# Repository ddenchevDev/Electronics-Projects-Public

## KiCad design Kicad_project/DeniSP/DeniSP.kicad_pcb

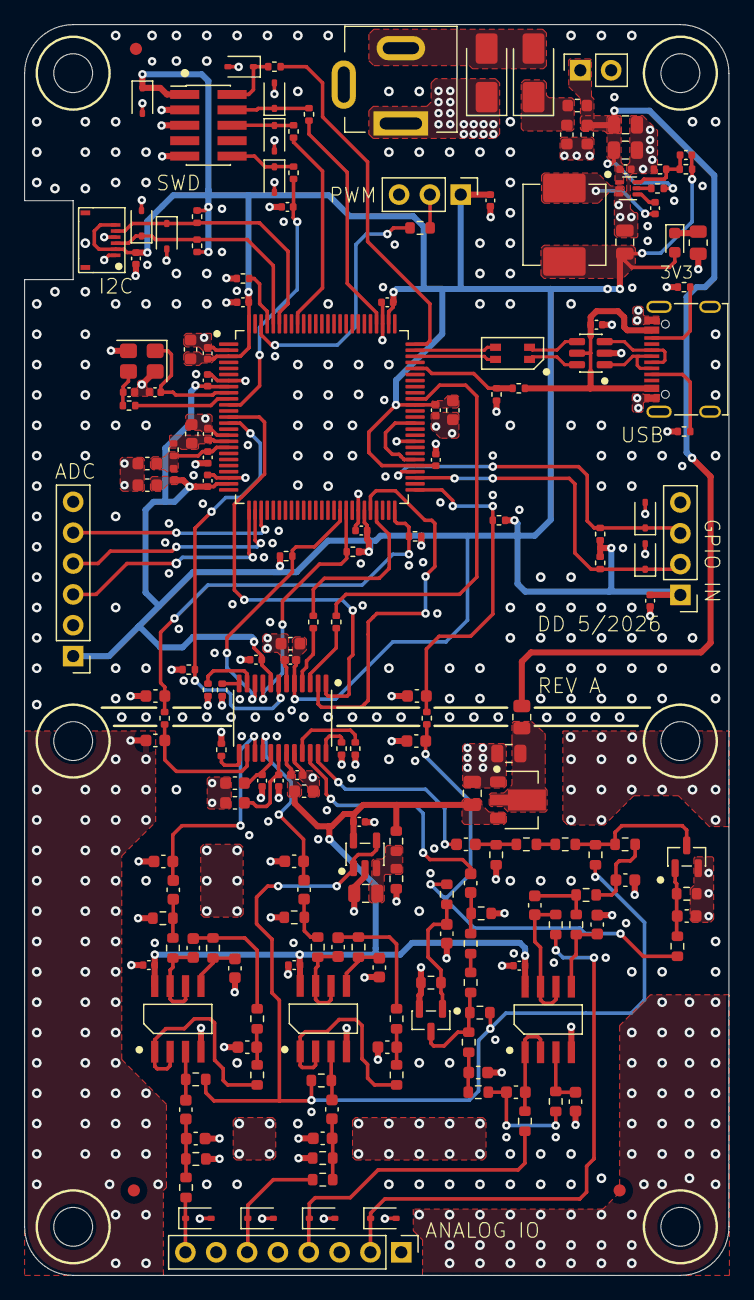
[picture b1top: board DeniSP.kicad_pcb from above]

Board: 4 copper layers, 58.0 x 103.0 mm, 194 parts (0 on the bottom side), 108 nets.

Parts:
C100, C101, C209, C212, C213, C221, C301, C305: 1u; C_0603_1608Metric
C102, C103, C104, C106, C107, C110: 22u; C_0805_2012Metric
C105, C108, C109, C202, C203, C204, C205, C206, C207, C208, C210, C211, C214, C215, C218, C219, C220, C222, C302, C303, C304, C312, C314, C320, C326, C336: 100n; C_0402_1005Metric
C111: 47pf; C_0402_1005Metric
C201, C313, C327, C328, C337, C338: 10u; C_0603_1608Metric
C216, C217: 14p; C_0402_1005Metric
C306, C316: 3.3u; C_0603_1608Metric
C307, C308, C317, C318: 2.2n; C_0603_1608Metric
C309, C319: 330p; C_0603_1608Metric
C310, C311, C341, C342: 2u2; C_0603_1608Metric
C315: 47u; C_0603_1608Metric
C321, C325, C331, C335: 150p; C_0603_1608Metric
C322, C332: 100n; C_0603_1608Metric
C323, C324, C333, C334: 1n; C_0603_1608Metric
C330, C340: DNP; C_0603_1608Metric
D100: SMAJ7.0CA; D_SMA
D101: SS14; D_SMA
D102: GREEN; LED_0603_1608Metric
D202, D203, D204, D205, D206, D207, D208, D209, D210, D300, D301, D302, D303: PESD3V3L1BA,115; D_SOD-323
FL201: WCM3216F2SF-900T04; CMC_3216-4P
H1, H2, H3, H4, H5, H6: MountingHole; MountingHole_3.2mm_M3
J100: Barrel_Jack; BarrelJack_Kycon_KLDX-0202-xC_Horizontal
J101: Conn_01x02; PinSocket_1x02_P2.54mm_Vertical
J201: USB_C_Receptacle_USB2.0_16P; USB_C_Receptacle_G-Switch_GT-USB-7010ASV
J202: Conn_01x04; PinHeader_1x04_P2.54mm_Vertical
J203: Conn_01x03; PinHeader_1x03_P2.54mm_Vertical
J204: Conn_01x06; PinHeader_1x06_P2.54mm_Vertical
J205: FH34SRJ-6S-0.5SH(50); FPC_6
J206: 2x5.1.27mm; PinHeader_2x05_P1.27mm_Vertical_SMD
J300: Conn_01x08; PinHeader_1x08_P2.54mm_Vertical
L100: 10n; L_0603_1608Metric
L101: 22u; L_Changjiang_FXL0630
L201: 10n; L_0402_1005Metric
Q300, Q301: AO3400A; SOT-23
R100: 10R; R_0805_2012Metric
R101, R102, R215, R302, R319, R325, R336: 1k; R_0603_1608Metric
R103: 100k; R_0402_1005Metric
R104: 135k; R_0402_1005Metric
R105: 30k; R_0402_1005Metric
R106: 1k; R_0805_2012Metric
R201, R202, R313, R314, R315, R316, R347: 5k1; R_0402_1005Metric
R203: 10k; R_0402_1005Metric
R204: 33k; R_0402_1005Metric
R205: 82k; R_0402_1005Metric
R206, R221: 0R; R_0402_1005Metric
R207, R208, R209, R210: 4k7; R_0402_1005Metric
R211, R212, R213, R214: DNP; R_0402_1005Metric
R217, R218, R219, R220: 49R9; R_0402_1005Metric
R300, R317: 10k; R_0603_1608Metric
R301, R307, R318, R324: 68; R_0603_1608Metric
R303, R320, R326, R327, R337, R338: 2M2; R_0603_1608Metric
R304, R321: 3k9; R_0603_1608Metric
R305, R322, R330, R341: 12k; R_0603_1608Metric
R306, R323, R328, R339: 6k8; R_0603_1608Metric
R308, R309: 47; R_0402_1005Metric
R310: DNP_47k; R_0402_1005Metric
R311, R312: 2k2; R_0402_1005Metric
R329, R340: 22k; R_0603_1608Metric
R331, R332, R342, R343: 2k; R_0603_1608Metric
R333, R344: 0R; R_0603_1608Metric
R335, R346: 100k; R_0603_1608Metric
U100: HT7550-1; SOT-89-3
U101: MCP6001-E/OT; SOT-23-5
U102: SOT-563
U201: STM32F469VIT6; LQFP-100_14x14mm_P0.5mm
U202: USBLC6-2SC6; SOT-23-6
U300: CS4270-CZZR; TSSOP-24_4.4x7.8mm_P0.65mm
U301, U302, U303: OPA1652-AIDR; SOIC-8
Y201: 16MHz; Crystal_SMD_3225-4Pin_3.2x2.5mm

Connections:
+3V3: C110.1, C111.1, C201.1, C202.1, C203.1, C204.1, C205.1, C206.1, C207.1, C208.1, C209.1, C210.1, C213.1, C218.1, C219.1, C222.1, C301.1, C302.1, C303.1, D102.2 (A), D206.1, J202.1, J203.1, J204.1, J205.2, J205.6, J206.1, L101.2, L201.2, R104.2, R207.1, R208.1, R209.1, R210.1, R211.2, R212.2, R213.2, R214.2, U201.3 (VBAT), U201.8 (VDD), U201.24 (VDD), U201.45 (VDD), U201.55 (VDDDSI), U201.65 (VDDUSB), U201.77 (VDD), U201.100 (VDD), U300.5 (VD), U300.8 (VLC)
+5VA: C103.1, C105.2, C304.1, C305.1, C320.1, C326.1, C336.1, R101.2, U100.3 (VOUT), U101.5 (V+), U300.19 (VA), U301.8 (V+), U302.8 (V+), U303.8 (V+)
+9V: C101.1, C106.1, C107.1, C108.1, J101.1, L100.2, R100.1, R103.1, U102.1 (Vin)
+9V_FILT_5V0A: C102.1, R100.2, U100.2 (VIN)
/CODEC/AD0: R314.1, U300.11 (AD0/~CS/I2S/~LJ)
/CODEC/AD1: R315.1, U300.12 (AD1/CDIN/MDIV1)
/CODEC/AD2: R316.1, U300.13 (AD2/MDIV2)
/CODEC/CODEC_MCLK: R308.2, U300.3 (MCLK)
/CODEC/CODEC_NRST_FILT: C311.1, R313.2, U300.14 (~RST)
/CODEC/CODEC_SCLK: R309.2, U300.4 (SCLK)
/CODEC/FILT_PLUS: C314.1, C315.1, U300.18 (FIL+)
/CODEC/IN_BUFF_OUT_A: R328.1, U302.1, U302.2 (-)
/CODEC/IN_BUFF_OUT_B: R339.1, U303.1, U303.2 (-)
/CODEC/IN_BUF_A: C322.2, R327.2, U302.3 (+)
/CODEC/IN_BUF_B: C332.2, R338.2, U303.3 (+)
/CODEC/IN_FILTER_BUF_A: C325.2, R330.2, U302.5 (+)
/CODEC/IN_FILTER_BUF_B: C335.2, R341.2, U303.5 (+)
/CODEC/IN_REFILT_BUF_A: C309.2, R306.2, U301.3 (+)
/CODEC/IN_REFILT_BUF_B: C319.2, R323.2, U301.5 (+)
/CODEC/MUTEA: R311.1, U300.21 (~MUTEA)
/CODEC/MUTEB: R312.1, U300.24 (~MUTEB)
/CODEC/MUTE_FILT: C342.2, R333.1, R344.1, R347.2
/CODEC/MUTE_MOS_GATE_L: C330.1, Q300.1 (G), R333.2, R335.1
/CODEC/MUTE_MOS_GATE_R: C340.1, Q301.1 (G), R344.2, R346.1
/CODEC/OUT_FILTER_BUF_A: C324.1, R331.1, U302.6 (-), U302.7
/CODEC/OUT_FILTER_BUF_B: C334.1, R342.1, U303.6 (-), U303.7
/CODEC/OUT_REFILT_BUF_A: C308.1, R307.1, U301.1, U301.2 (-)
/CODEC/OUT_REFILT_BUF_B: C318.1, R324.1, U301.6 (-), U301.7
/CODEC/VQ: C312.1, C313.1, U300.17 (VQ)
/MCU/BOOT0: R203.2, U201.97 (BOOT0)
/MCU/CONN_NRST: D210.1, J206.10, R220.1
/MCU/CONN_SWCLK: D208.1, J206.4, R218.1
/MCU/CONN_SWDIO: D207.1, J206.2, R217.1
/MCU/CONN_SWO: D209.1, J206.6, R219.1
/MCU/HSE_IN: C216.1, U201.9 (PH0), Y201.1
/MCU/HSE_OUT: R206.2, U201.10 (PH1)
/MCU/LED_A: J203.2, R215.2
/MCU/USB_CONN_CC1: J201.A5 (CC1), R201.1
/MCU/USB_CONN_CC2: J201.B5 (CC2), R202.1
/MCU/VBUS_SENSE: R204.2, R205.1, U201.71 (PA9)
/MCU/VREF_PLUS: C214.1, C221.1, R221.2, U201.17 (VREF+)
/MCU/XTAL_IN: C217.1, R206.1, Y201.3
/Power/BST_C: C109.1, U102.4 (BST)
/Power/LED_C: D102.1 (K), R106.2
/Power/PI_FILT_IN: C100.1, D101.1 (K), L100.1
/Power/R_EN: R103.2, U102.5 (EN)
/Power/SW_L: C109.2, L101.1, U102.2 (SW)
/Power/VREF: C104.1, R101.1, R102.2, U101.3 (+)
/Power/V_FB: C111.2, R104.1, R105.2, U102.6 (FB)
ADC1_IN1: J204.3, U201.26 (PA5)
ADC1_IN2: J204.4, U201.27 (PA6)
ADC1_IN3: J204.5, U201.28 (PA7)
ANALOG_IN_A: C327.1, C328.2, U300.15 (AINA)
ANALOG_IN_B: C337.1, C338.2, U300.16 (AINB)
ANALOG_OUT_A: C306.1, U300.22 (OUTA)
ANALOG_OUT_B: C316.1, U300.23 (OUTB)
CODEC_NRST: C310.1, R214.1, R313.1, U201.50 (PD8)
DIGITAL_IN_1: D202.1, J202.2, R212.1, U201.53 (PD14)
DIGITAL_IN_2: D203.1, J202.3, R211.1, U201.54 (PD15)
GND: C100.2, C101.2, C102.2, C103.2, C104.2, C105.1, C106.2, C107.2, C108.2, C110.2, C201.2, C202.2, C203.2, C204.2, C205.2, C206.2, C207.2, C208.2, C209.2, C210.2, C211.2, C212.2, C213.2, C214.2, C215.1, C216.2, C217.2, C218.2, C219.2, C220.2, C221.2, C222.2, C301.2, C302.2, C303.2, C304.2, C305.2, C307.1, C309.1, C310.2, C311.2, C312.2, C313.2, C314.2, C315.2, C317.1, C319.1, C320.2, C321.2, C323.1, C325.1, C326.2, C328.1, C330.2, C331.2, C333.1, C335.1, C336.2, C338.1, C340.2, C341.1, C342.1, D100.1 (A1), D202.2, D203.2, D204.2, D205.2, D206.2, D207.2, D208.2, D209.2, D210.2, D300.2, D301.2, D302.2, D303.2, J100.1, J101.2, J201.A1 (GND), J201.A12 (GND), J201.B1 (GND), J201.B12 (GND), J202.4, J203.3, J204.2, J204.6, J205.1, J205.4, J206.3, J206.5, J206.9, J300.1, J300.3, J300.5, J300.7, Q300.2 (S), Q301.2 (S), R102.1, R105.1, R106.1, R201.2, R202.2, R203.1, R205.2, R300.2, R310.2, R311.2, R312.2, R314.2, R315.2, R316.2, R317.2, R326.2, R332.1, R335.2, R337.2, R343.1, R346.2, U100.1 (GND), U101.2 (V-), U102.3 (GND), U201.2 (VSS), U201.7 (VSS), U201.16 (VSSA), U201.23 (VSS), U201.44 (VSS), U201.59 (VSSDSI), U201.78 (VSS), U202.2 (GND), U300.6 (DGND), U300.20 (AGND), U301.4 (V-), U302.4 (V-), U303.4 (V-), Y201.2 (G), Y201.4 (G)
I2C1_SCL: R209.2, U201.41 (PB10), U300.10 (SCL/CCLK/M0)
I2C1_SDA: R210.2, U201.42 (PB11), U300.9 (SDA/CDOUT/M1)
I2C2_SCL: D205.1, J205.5, R207.2, U201.95 (PB6)
I2C2_SDA: D204.1, J205.3, R208.2, U201.96 (PB7)
I2S2_CK: R309.1, U201.47 (PB13)
I2S2_MCK: R308.1, U201.66 (PC6)
I2S2_SD: U201.13 (PC1), U300.1 (SDIN)
I2S2_WS: U201.46 (PB12), U300.2 (LRCLK)
I2S2_ext_SD: R310.1, U201.14 (PC2), U300.7 (SDOUT)
INPUT_L: D302.1, J300.8, R325.1
INPUT_R: D303.1, J300.6, R336.1
LED1_C: R215.1, U201.98 (PB8)
MUTE_CTRL: C341.2, R213.1, R347.1, U201.51 (PD9)
MUTE_SHUNT_L: Q300.3 (D), R302.2, R303.2, R304.1
MUTE_SHUNT_R: Q301.3 (D), R319.2, R320.2, R321.1
NRST: C220.1, R220.2, U201.11 (NRST)
unnamed: C306.2, R300.1, R301.1
unnamed: C307.2, R304.2, R305.1
unnamed: C308.2, R305.2, R306.1
unnamed: C316.2, R317.1, R318.1
unnamed: C317.2, R321.2, R322.1
unnamed: C318.2, R322.2, R323.1
unnamed: C321.1, C322.1, R325.2, R326.1
unnamed: C323.2, R328.2, R329.1
unnamed: C324.2, R329.2, R330.1
unnamed: C327.2, R331.2, R332.2
unnamed: C331.1, C332.1, R336.2, R337.1
unnamed: C333.2, R339.2, R340.1
unnamed: C334.2, R340.2, R341.1
unnamed: C337.2, R342.2, R343.2
unnamed: R301.2, R302.1
unnamed: R318.2, R319.1
OUTPUT_L: D300.1, J300.4, R307.2
OUTPUT_R: D301.1, J300.2, R324.2
SWCLK: R218.2, U201.79 (PA14)
SWDIO: R217.2, U201.75 (PA13)
SWO: R219.2, U201.92 (PB3)
USB_CMC_D+: FL201.4, U202.4 (I/O2)
USB_CMC_D-: FL201.1, U202.6 (I/O1)
USB_CONN_D+: J201.A6 (D+), J201.B6 (D+), U202.3 (I/O2)
USB_CONN_D-: J201.A7 (D-), J201.B7 (D-), U202.1 (I/O1)
USB_FS_D+: FL201.3, U201.74 (PA12)
USB_FS_D-: FL201.2, U201.73 (PA11)
VBUS: C215.2, J201.A4 (VBUS), J201.A9 (VBUS), J201.B4 (VBUS), J201.B9 (VBUS), R204.1, U202.5 (VBUS)
VCC: D100.2 (A2), D101.2 (A), J100.2
VCOM: R303.1, R320.1, R327.1, R338.1, U101.1, U101.4 (-)
VDD12DSI: U201.56 (VCAPDSI), U201.62 (VDD12DSI)
VDDA: C211.1, C212.1, L201.1, R221.1, U201.18 (VDDA)
